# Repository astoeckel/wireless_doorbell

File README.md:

# Wireless Doorbell
**A hopelessly overengineered wireless doorbell transmitter (and Raspberry Pi AVR prototyping HAT)**

> **Warning**  
> This project is provided as-is and likely not of use to anyone else; at least not without modifications. Note that:
> 1. The PCB (especially the AC supply) was designed for parts the author had lying around. Many of these parts may be obsolete.
> 2. This project solves a very niche problem.
> 3. The firmware uses plain-text wireless transmission without encryption or signatures. This is fine for the author's use case, where all an adversary can accomplish is to wirelessly ring the doorbell. A sneaky hacker could of course just press the doorbell button on the street to the same effect.
>
> **The author of this repository takes no responsibility for any damage resulting from using the electronic devices described here.**
> **You are responsible for making sure that operating these devices meets all relevant regulatory requirements in your region.**

This repository contains the PCB and firmware for a Si4463-based (on a HopeRF RFM26W module) wireless doorbell operating on the 433 MHz ISM band.
The Si4463 is controlled using an ATmega168 µC (the project requires about 6kiB of flash memory).

Doorbell button presses are transmitted wirelessly between two of these PCBs.
One of the PCBs serves as a Raspberry Pi HAT, where button press events are forwarded via UART to [OpenHAB](https://www.openhab.org/) (using [Serial Bridge and Serial Device](https://www.openhab.org/addons/bindings/serial/)).
In turn, OpenHAB has a rule that causes all SIP phones in the house to ring via [FemtoSIP](https://github.com/astoeckel/femtosip).

The left side of the PCB is a Raspberry Pi compatible AVR Microcontroller HAT (for the ATmega168/ATMega328 family) with Arduino-compatible pin headers and space for the HopeRF RFM26W module (note that this module seems to be obsolete).
The right side of the PCB is an low-voltage AC power supply with 50 Hz pulse extraction and is designed to be sawed off if not in use.

Since PCB prototyping services often produce at least 5-10 PCBs, the PCB was designed with some versatility in mind.
Correspondingly, the left side of the PCB has far more pin headers as necessary, and can be used as a general-purpose ATmega168/328 development board.
Specifically, the AVR can be programmed directly by the Raspberry Pi (no ISP programmer required) and can communicate via UART (the schematic suggests the use of a 14.7456 MHz crystal for stable high-speed communication).

## Overview

The above diagram depicts how the PCB is intended to be used.
One instance of the PCB is directly powered by the low-voltage doorbell AC transformer; the other instance is powered by the 5V power supply of a Raspberry Pi.

Button presses are recognized by the doorbell button shorting out the yellow and black wires in the above diagram.
Correspondingly, the 50 Hz oscillations disappear on the yellow wire; this is recognized by the ATmega168 microcontroller which sends a few digital packets of the form
```
$DBG,<BUTTON PRESSED>,<SEQ>
```
to the receiver at a baud rate of 10kbps.
`<BUTTON PRESSED>` is set to `1` if the 50 Hz signal goes away; it is set to `0` once the signal reappears.
Every packet is repeated five times; with each repetition `<SEQ>` is incremented by one (starting from `0`).

## Schematics and Gerber files

* **Gerber files**  
  The Gerber files used for production can be found in the `gerber` folder (the author is not aware of any bugs on the PCB).
* **Schematic and KiCAD sources**  
  The KiCAD source files are in the `kicad` folder. A printout of the schematics in [PDF form](doc/schematics.pdf) can be found in the `doc` folder.

## Firmware

The firmware is located in the `code` folder.
It uses `avr-gcc` and `avr-libc`, as well as `avrdude` with the [linuxspi patches](https://github.com/kcuzner/avrdude).

It can be compiled and flashed using [meson](https://mesonbuild.com/) as follows:
```sh
cd code; mkdir -p build
meson setup --cross-file ../avr-unknown-gcc.txt ..
ninja
ninja flash  # Requires avrdude with linuxspi when flashing directly from the RPi
```

## Usage

The firmware automatically decides whether it acts as the receiver or transmitter depending on the presence of the 50 Hz pulse from the yellow wire in the above diagram.
Once a stable series of 50 Hz pulse are received, the device is in “transmitter” mode.

### Antenna
Note that the antenna on the board is designed for 868 MHz and does not have a large gain (close the solder bridge `J` on the board to activate the internal antenna).
In the final device, I'm using [this antenna](https://www.instructables.com/433-MHz-Coil-loaded-antenna/) ([PDF instructions by Ben Schueler](https://drive.google.com/file/d/1E9KPAPJrZRgGLOQqwd2-3-Px0MuSVreY/view)) soldered directly to the RFM26W module (the antenna is not connected to the PCB).

### Receiver

1. Connect UART RX/TX pins and 5V power (use a baud rate of 115200) to Raspberry Pi
2. The `RX` LED should be illuminated; the LED will blink rapidly if the receiver receives any data.
3. Incoming messages will be printed as a one-line JSON-encoded string to UART
4. Shortly pressing the SMD button on the board will send a `PING` request. If any board responds with a `PONG`, both the `RX` and `TX` LED will blink rapidly for two seconds. *Note:* The transmitter is usually in energy saving mode and will not respond. Wake the transmitter up by pressing the SMD button there.
5. Pressing the SMD button for at least 3 seconds will reset the µC on the board.

### Transmitter
1. Connect the three doorbell wires as indicated in the diagram above.
2. The `RX` led will blink once every second if the 50 Hz pulse has been recognized; the board will go to a 3-4mA power-save mode (this is to prevent the linear voltage regulator from becoming too hot).
3. If the 50 Hz signal goes away, the transmitter will send a message to the receiver as described above. The `TX` LED should blink rapidly.
4. Shortly pressing the SMD button will send a `PING` request and rapidly blink both LEDs if it receives a response. Furthermore, the transmitter will leave power-save mode for one minute; it can now respond with `PONG` to `PING` messages issued by the receiver.
5. Pressing the SMD button for 3 seconds will reset the µC on the board.

## License

Note that this project consists of both hardware and to a smaller portion of software. Both parts are made available under different licenses.

### Hardware schematics

    Copyright Andreas Stöckel 2022.
    
    This documentation describes Open Hardware and is licensed under the
    CERN OHL v. 1.2. You may redistribute and modify this documentation under
    the terms of the CERN OHL v.1.2. (http://ohwr.org/cernohl). This
    documentation is distributed WITHOUT ANY EXPRESS OR IMPLIED WARRANTY,
    INCLUDING OF MERCHANTABILITY, SATISFACTORY QUALITY AND FITNESS FOR A
    PARTICULAR PURPOSE. Please see the CERN OHL v.1.2 for applicable conditions.

### Software (AVR firmware and host programs)

    This program is free software: you can redistribute it and/or modify
    it under the terms of the GNU General Public License as published by
    the Free Software Foundation, either version 3 of the License, or
    (at your option) any later version.
    
    This program is distributed in the hope that it will be useful,
    but WITHOUT ANY WARRANTY; without even the implied warranty of
    MERCHANTABILITY or FITNESS FOR A PARTICULAR PURPOSE.  See the
    GNU General Public License for more details.
    
    You should have received a copy of the GNU General Public License
    along with this program.  If not, see <http://www.gnu.org/licenses/>.

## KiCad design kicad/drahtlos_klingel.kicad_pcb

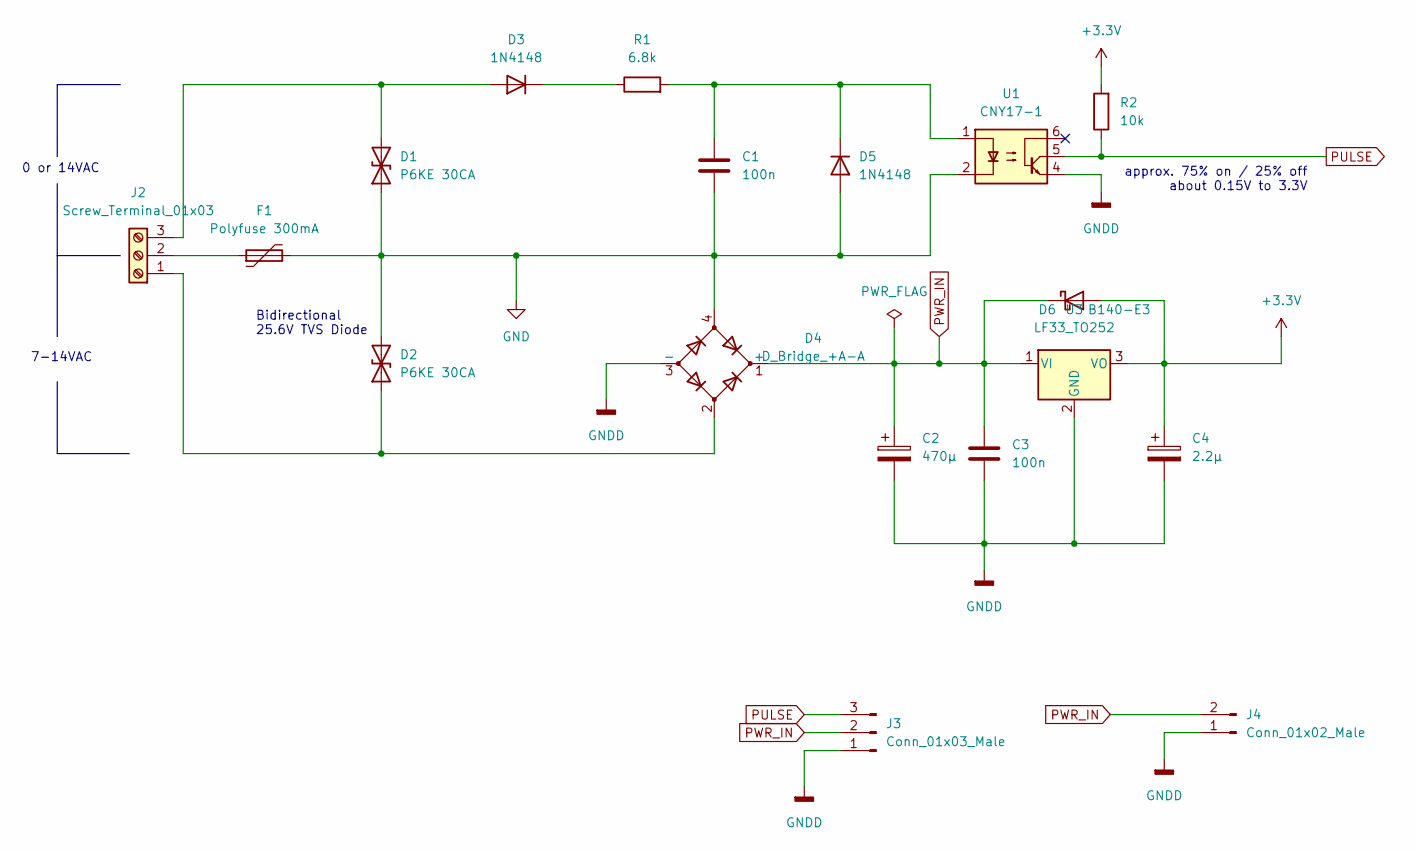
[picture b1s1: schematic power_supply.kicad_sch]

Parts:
C1: 100n; C_Rect_L7.0mm_W2.5mm_P5.00mm
C2: 470µ; CP_Radial_D12.5mm_P7.50mm
C3: 100n; C_1206_3216Metric_Pad1.33x1.80mm_HandSolder
C4: 2.2µ; C_1206_3216Metric_Pad1.33x1.80mm_HandSolder
D1, D2: P6KE 30CA; D_DO-15_P12.70mm_Horizontal
D3, D5: 1N4148; D_DO-35_SOD27_P10.16mm_Horizontal
D4: D_Bridge_+A-A; Diode_Bridge_Round_D9.8mm
D6: B140-E3; D_SMA
F1: Polyfuse 300mA; R_Axial_DIN0204_L3.6mm_D1.6mm_P7.62mm_Horizontal
J2: Screw_Terminal_01x03; TerminalBlock_bornier-3_P5.08mm
J3: Conn_01x03_Male; PinHeader_1x03_P2.54mm_Vertical
J4: Conn_01x02_Male; PinHeader_1x02_P2.54mm_Vertical
R1: 6.8k; R_Axial_DIN0204_L3.6mm_D1.6mm_P7.62mm_Horizontal
R2: 10k; R_1206_3216Metric_Pad1.30x1.75mm_HandSolder
U1: CNY17-1; DIP-6_W7.62mm
U3: LF33_TO252; TO-252-2

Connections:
+3.3V: C4.1, D6.2 (A), R2.2, U3.3 (VO); also elsewhere on the board
GND: C1.2, D1.1 (A1), D2.2 (A2), D4.4, D5.2 (A), F1.2, U1.2
GNDD: C2.2, C3.2, C4.2, D4.3 (-), J3.1, J4.1, U1.4, U3.2 (GND); also elsewhere on the board
unnamed: C1.1, D5.1 (K), R1.2, U1.1
unnamed: D1.2 (A2), D3.2 (A), J2.3
unnamed: D2.1 (A1), D4.2, J2.1
unnamed: D3.1 (K), R1.1
unnamed: F1.1, J2.2
PULSE: J3.3, R2.1, U1.5; also elsewhere on the board
PWR_IN: C2.1, C3.1, D4.1 (+), D6.1 (K), J3.2, J4.2, U3.1 (VI); also elsewhere on the board

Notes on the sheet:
0 or 14VAC
Bidirectional 25.6V TVS Diode
7-14VAC
approx. 75% on / 25% off about 0.15V to 3.3V

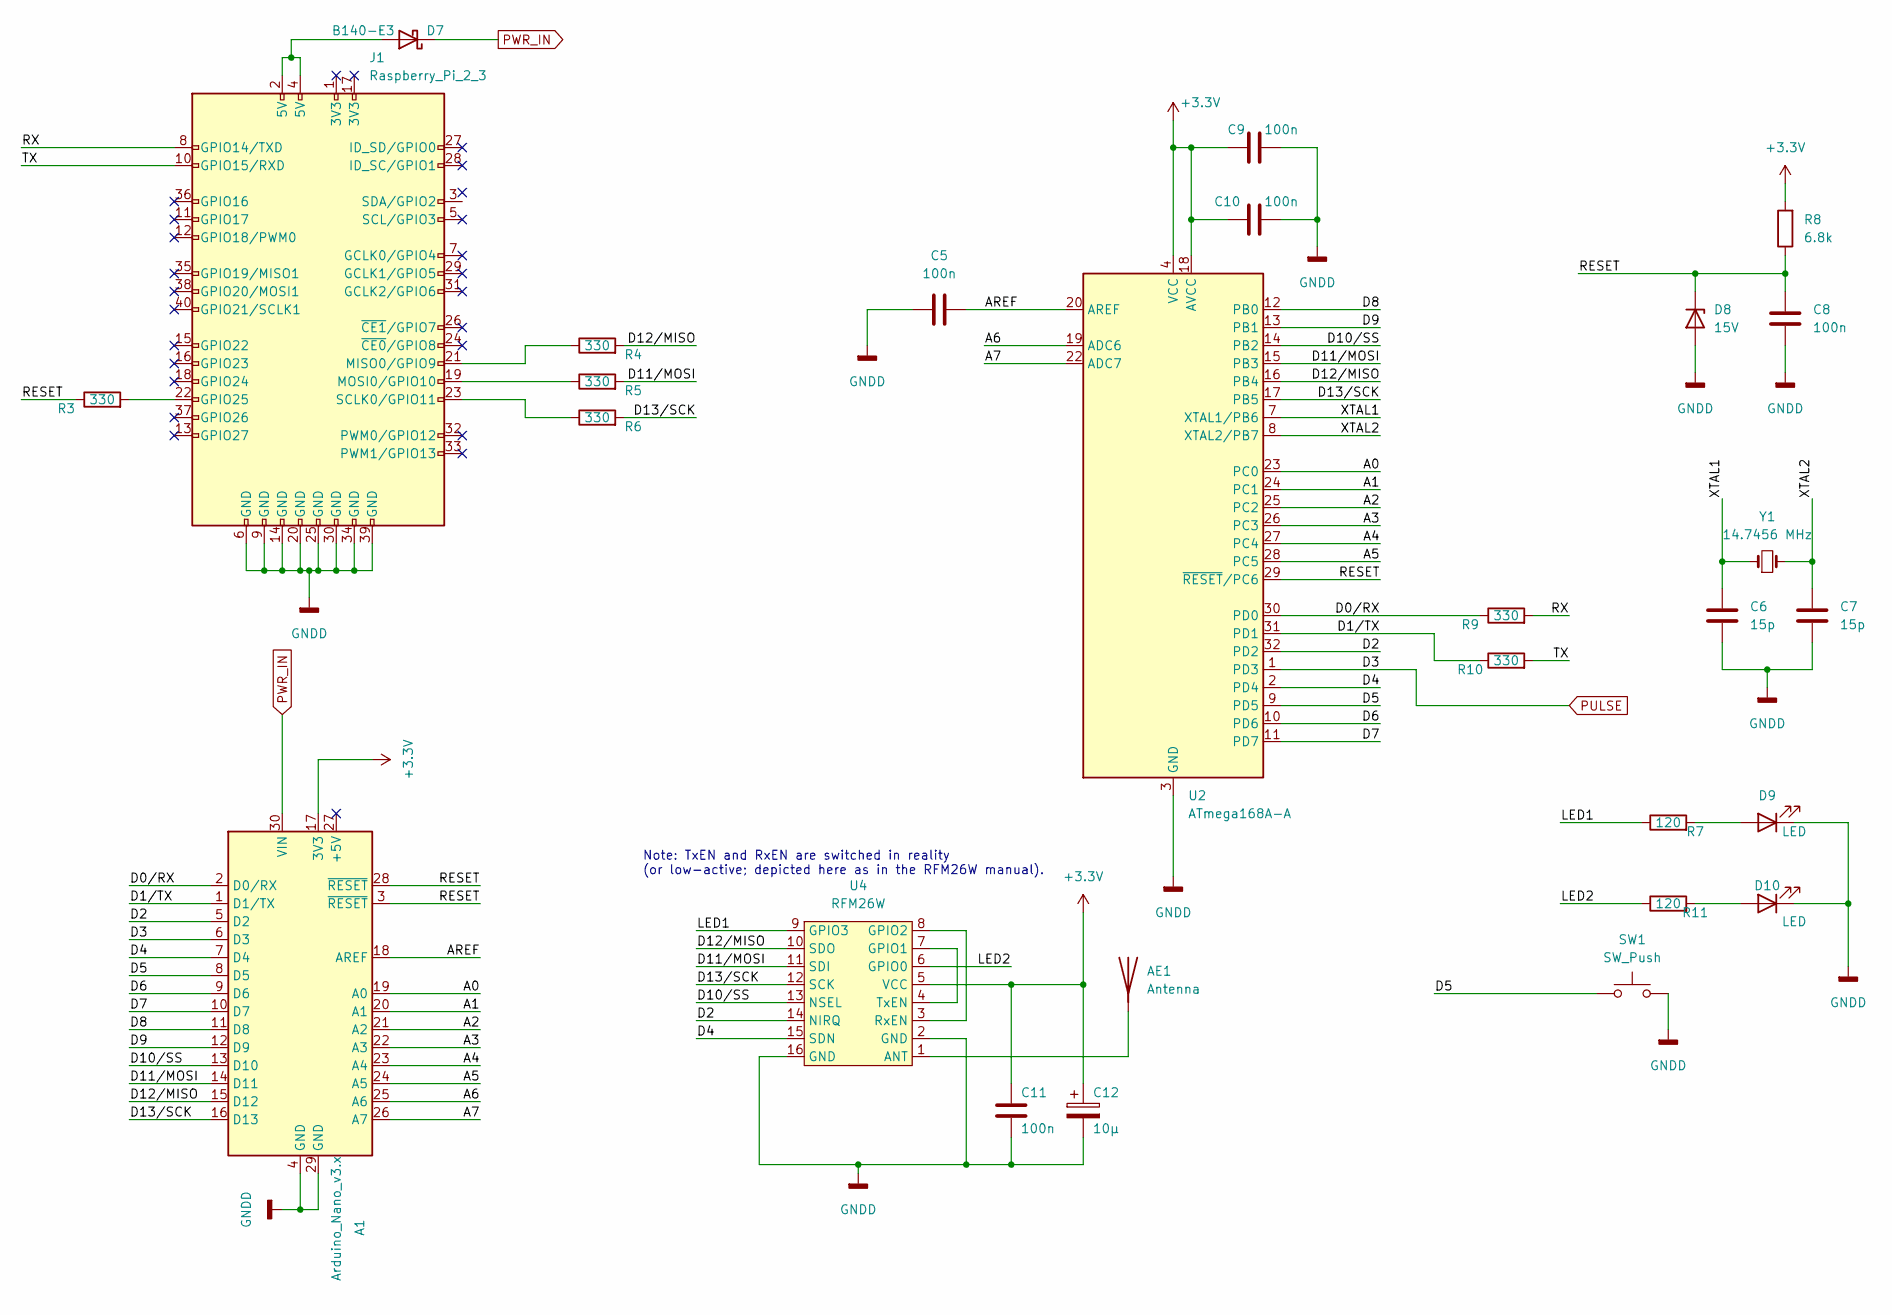
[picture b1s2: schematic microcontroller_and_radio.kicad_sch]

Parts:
A1: Arduino_Nano_v3.x; Arduino_Nano
AE1: Antenna; Texas_SWRA416_868MHz_915MHz
C5, C8, C9, C10, C11: 100n; C_1206_3216Metric_Pad1.33x1.80mm_HandSolder
C6, C7: 15p; C_0805_2012Metric_Pad1.18x1.45mm_HandSolder
C12: 10µ; CP_Radial_D6.3mm_P2.50mm
D7: B140-E3; D_SMA
D8: 15V; SOT-23
D9, D10: LED; LED_1206_3216Metric_Pad1.42x1.75mm_HandSolder
J1: Raspberry_Pi_2_3; PinSocket_2x20_P2.54mm_Vertical
R3, R4, R5, R6, R9, R10: 330; R_1206_3216Metric_Pad1.30x1.75mm_HandSolder
R7, R11: 120; R_1206_3216Metric_Pad1.30x1.75mm_HandSolder
R8: 6.8k; R_1206_3216Metric_Pad1.30x1.75mm_HandSolder
SW1: SW_Push; SW_SPST_EVQQ2
U2: ATmega168A-A; TQFP-32_7x7mm_P0.8mm
U4: RFM26W; rfm26w
Y1: 14.7456 MHz; Crystal_SMD_HC49-SD

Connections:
+3.3V: A1.17 (3V3), C9.1, C10.2, C11.1, C12.1, R8.2, U2.4 (VCC), U2.6 (VCC), U2.18 (AVCC), U4.5 (VCC); also elsewhere on the board
/microcontroller_and_radio/A0: A1.19 (A0), U2.23 (PC0)
/microcontroller_and_radio/A1: A1.20 (A1), U2.24 (PC1)
/microcontroller_and_radio/A2: A1.21 (A2), U2.25 (PC2)
/microcontroller_and_radio/A3: A1.22 (A3), U2.26 (PC3)
/microcontroller_and_radio/A4: A1.23 (A4), U2.27 (PC4)
/microcontroller_and_radio/A5: A1.24 (A5), U2.28 (PC5)
/microcontroller_and_radio/A6: A1.25 (A6), U2.19 (ADC6)
/microcontroller_and_radio/A7: A1.26 (A7), U2.22 (ADC7)
/microcontroller_and_radio/AREF: A1.18 (AREF), C5.2, U2.20 (AREF)
/microcontroller_and_radio/D0/RX: A1.2 (D0/RX), R9.1, U2.30 (PD0)
/microcontroller_and_radio/D1/TX: A1.1 (D1/TX), R10.1, U2.31 (PD1)
/microcontroller_and_radio/D2: A1.5 (D2), U2.32 (PD2), U4.14 (NIRQ)
/microcontroller_and_radio/D4: A1.7 (D4), U2.2 (PD4), U4.15 (SDN)
/microcontroller_and_radio/D5: A1.8 (D5), SW1.1, U2.9 (PD5)
/microcontroller_and_radio/D6: A1.9 (D6), U2.10 (PD6)
/microcontroller_and_radio/D7: A1.10 (D7), U2.11 (PD7)
/microcontroller_and_radio/D8: A1.11 (D8), U2.12 (PB0)
/microcontroller_and_radio/D9: A1.12 (D9), U2.13 (PB1)
/microcontroller_and_radio/D10/SS: A1.13 (D10), U2.14 (PB2), U4.13 (NSEL)
/microcontroller_and_radio/D11/MOSI: A1.14 (D11), R5.2, U2.15 (PB3), U4.11 (SDI)
/microcontroller_and_radio/D12/MISO: A1.15 (D12), R4.2, U2.16 (PB4), U4.10 (SDO)
/microcontroller_and_radio/D13/SCK: A1.16 (D13), R6.2, U2.17 (PB5), U4.12 (SCK)
/microcontroller_and_radio/LED1: R7.1, U4.9 (GPIO3)
/microcontroller_and_radio/LED2: R11.1, U4.6 (GPIO0)
/microcontroller_and_radio/RESET: A1.3 (~RESET), A1.28 (~RESET), C8.1, D8.1 (K), R3.1, R8.1, U2.29 (~RESET/PC6)
/microcontroller_and_radio/RX: J1.8 (GPIO14/TXD), R9.2
/microcontroller_and_radio/TX: J1.10 (GPIO15/RXD), R10.2
/microcontroller_and_radio/XTAL1: C6.1, U2.7 (XTAL1/PB6), Y1.1
/microcontroller_and_radio/XTAL2: C7.1, U2.8 (XTAL2/PB7), Y1.2
GNDD: A1.4 (GND), A1.29 (GND), C5.1, C6.2, C7.2, C8.2, C9.2, C10.1, C11.2, C12.2, D8.2 (A), D9.1 (K), D10.1 (K), J1.6 (GND), J1.9 (GND), J1.14 (GND), J1.20 (GND), J1.25 (GND), J1.30 (GND), J1.34 (GND), J1.39 (GND), SW1.2, U2.3 (GND), U2.5 (GND), U2.21 (GND), U4.2 (GND), U4.16 (GND); also elsewhere on the board
unnamed: AE1.1 (A), U4.1 (ANT)
unnamed: D7.2 (A), J1.2 (5V), J1.4 (5V)
unnamed: D9.2 (A), R7.2
unnamed: D10.2 (A), R11.2
unnamed: J1.19 (MOSI0/GPIO10), R5.1
unnamed: J1.21 (MISO0/GPIO9), R4.1
unnamed: J1.22 (GPIO25), R3.2
unnamed: J1.23 (SCLK0/GPIO11), R6.1
unnamed: U4.3 (RxEN), U4.8 (GPIO2)
unnamed: U4.4 (TxEN), U4.7 (GPIO1)
PULSE: A1.6 (D3), U2.1 (PD3); also elsewhere on the board
PWR_IN: A1.30 (VIN), D7.1 (K); also elsewhere on the board

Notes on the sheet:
Note: TxEN and RxEN are switched in reality (or low-active; depicted here as in the RFM26W manual).

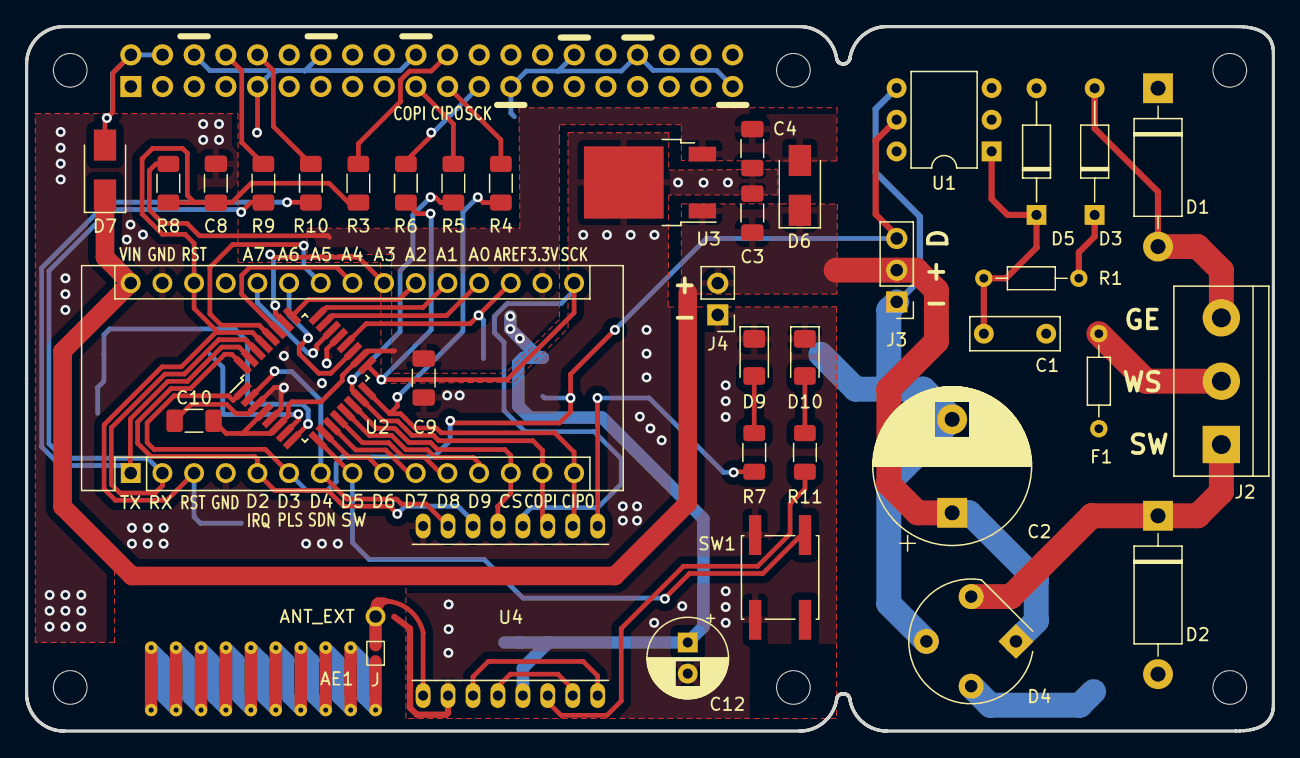
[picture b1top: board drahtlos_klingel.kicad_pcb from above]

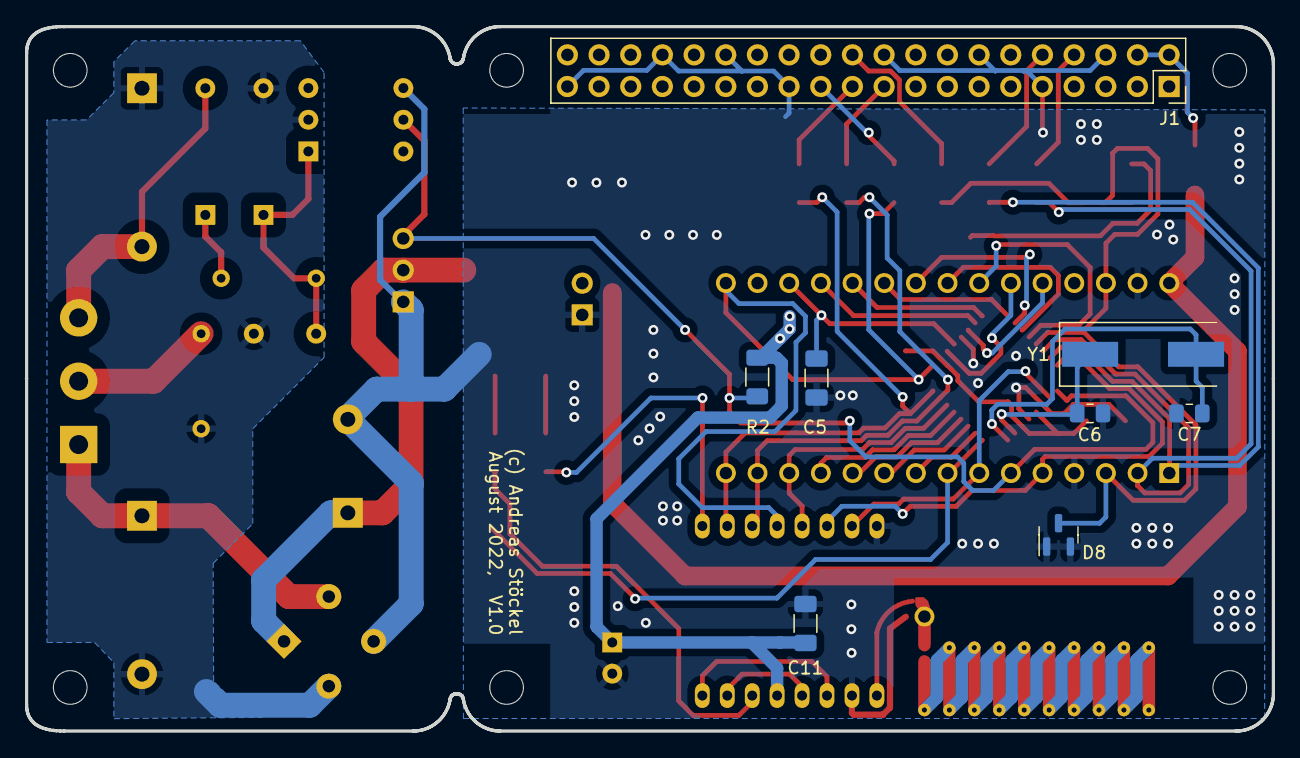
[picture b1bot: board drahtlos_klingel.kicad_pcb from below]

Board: 2 copper layers, 100.0 x 56.5 mm, 46 parts (8 on the bottom side), 49 nets.

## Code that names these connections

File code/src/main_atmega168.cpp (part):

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			// Reset last_falling_edge_ticks to prevent overflows of delta
			last_falling_edge_ticks = cur_ticks;

			// Is the pulse pin still high? If not, we might just be running
			// out of power.
			if (pin_state) {
				return Pressed;
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		if ((left_on != last_left_on) || (right_on != last_right_on)) {
			last_left_on = left_on;
			last_right_on = right_on;
			auto gpio0 = right_on ? Si4463::GPIOMode::Drive_High
			                      : Si4463::GPIOMode::Drive_Low;
			auto gpio3 = left_on ? Si4463::GPIOMode::Drive_High
			                     : Si4463::GPIOMode::Drive_Low;
			Si4463::gpio_pin_cfg(Si4463::GPIOConfig()
			                         .gpio0(gpio0)
			                         .gpio1(Si4463::GPIOMode::Unchanged)
			                         .gpio2(Si4463::GPIOMode::Unchanged)
			                         .gpio3(gpio3));
		}
	}

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	// For the first 500ms, and while the button is held, turn both LEDs on;
	// this is to give a visual indication of the reset happening.
	Si4463::gpio_pin_cfg(Si4463::GPIOConfig()
	                         .gpio0(Si4463::GPIOMode::Drive_High)
	                         .gpio1(Si4463::GPIOMode::Unchanged)
	                         .gpio2(Si4463::GPIOMode::Unchanged)
	                         .gpio3(Si4463::GPIOMode::Drive_High));
	Watchdog::disable();
	_delay_ms(500);
	while (!Platform::sample_button_pin()) {
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	};
	Watchdog::enable();
	Si4463::gpio_pin_cfg(Si4463::GPIOConfig()
	                         .gpio0(Si4463::GPIOMode::Drive_Low)
	                         .gpio1(Si4463::GPIOMode::Unchanged)
	                         .gpio2(Si4463::GPIOMode::Unchanged)
	                         .gpio3(Si4463::GPIOMode::Drive_Low));
	Watchdog::disable();
	_delay_ms(500);
	Watchdog::enable();

	// Configure GPIO1 and GPIO2 to drive the Tx/Rx switch
	Si4463::gpio_pin_cfg(Si4463::GPIOConfig()
	                         .gpio0(Si4463::GPIOMode::Unchanged)
	                         .gpio1(Si4463::GPIOMode::Rx_State)
	                         .gpio2(Si4463::GPIOMode::Tx_State)
	                         .gpio3(Si4463::GPIOMode::Unchanged));

	// Enable µC interrupts
	sei();
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
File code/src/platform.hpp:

/*
 *  AVR/Si4463 Wireless Doorbell
 *  Copyright (C) 2022  Andreas Stöckel
 *
 *  This program is free software: you can redistribute it and/or modify
 *  it under the terms of the GNU General Public License as published by
 *  the Free Software Foundation, either version 3 of the License, or
 *  (at your option) any later version.
 *
 *  This program is distributed in the hope that it will be useful,
 *  but WITHOUT ANY WARRANTY; without even the implied warranty of
 *  MERCHANTABILITY or FITNESS FOR A PARTICULAR PURPOSE.  See the
 *  GNU General Public License for more details.
 *
 *  You should have received a copy of the GNU General Public License
 *  along with this program.  If not, see <https://www.gnu.org/licenses/>.
 */

#pragma once

#define F_CPU 14745600ULL

#include <avr/io.h>
#include <stdint.h>
#include <util/delay.h>


namespace Platform {

static inline void delay_us(double us) {
	_delay_us(us);
}

static inline void delay_ms(double ms) {
	_delay_ms(ms);
}

static inline void set_bit(volatile uint8_t &port, uint8_t pin, bool x)
{
	port = x ? (port | (1 << pin)) : (port & ~(1 << pin));
}

static inline bool get_bit(volatile uint8_t &pinreg, uint8_t pin)
{
	return (pinreg & (1 << pin)) == (1 << pin);
}

static inline bool sample_radio_irq_pin() {
	return get_bit(PIND, 2);
}

static inline bool sample_pulse_pin() {
	return get_bit(PIND, 3);
}

static inline bool sample_button_pin() {
	return get_bit(PIND, 5);
}

static inline void init_gpio() {
	// Port A: N/A

	// Port B:
	// Pin 0: CLKO
	// Pin 1: NC
	// Pin 2: Si4463 SS    O
	// Pin 3: Si4463 MOSI  O
	// Pin 4: Si4463 MISO  I
	// Pin 5: Si4463 SCK   O
	// Pin 6: N/A (XTAL1)
	// Pin 7: N/A (XTAL2)
	DDRB = 0b0010'1101;
	PORTB = 0b1101'0000;

	// Port C:
	// Pin 0: NC
	// Pin 1: NC
	// Pin 2: NC
	// Pin 3: NC
	// Pin 4: NC
	// Pin 5: NC
	// Pin 6: N/A (RESET)
	// Pin 7: NC
	DDRC = 0b0000'0000;
	PORTC = 0b1111'1111;

	// Port D:
	// Pin 0: RXD I
	// Pin 1: TXD O
	// Pin 2: Si4463 IRQ   I
	// Pin 3: PULSE I (already has a hw pull-up)
	// Pin 4: Si4463 SDN   O
	// Pin 5: BUTTON I
	// Pin 6: NC
	// Pin 7: DBG O
	DDRD  = 0b1001'0010;
	PORTD = 0b0110'0101;

	// Setup IRQs on PIND2 (INT0) and PIND3 (INT1)
	EICRA = (1 << ISC11) | (1 << ISC01);
	EIMSK = (1 << INT1) | (1 << INT0);
}

static inline void radio_reset(bool value) { set_bit(PORTD, 4, value); }

static inline void radio_select(bool value) { set_bit(PORTB, 2, value); }

static inline void radio_spi_init() {
	// Enable SPI with CHPA = 0; use F_CPU / 2
	SPCR = (1 << SPE) | (1 << MSTR);
	//SPSR = (1 << SPI2X);
}

static inline uint8_t radio_spi_send(uint8_t x)
{
	SPDR = x;
	while (!(SPSR & (1 << SPIF))) {}
	return SPDR;
}

}

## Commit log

2022-09-10 Working code version
2022-09-11 Working reset
2022-09-11 Factor out LED state machine
2022-09-11 Add Kicad project and documentation
